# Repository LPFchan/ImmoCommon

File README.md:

# Immogen — Ninebot G30 BLE Immobilizer

**Immogen** is a three-part BLE immobilizer system for the Ninebot Max G30, consisting of **[Uguisu](https://github.com/LPFchan/Immogen/tree/main/Uguisu#readme)** (key fob), **[Guillemot](https://github.com/LPFchan/Immogen/tree/main/Guillemot#readme)** (deck receiver), and **[Whimbrel](https://github.com/LPFchan/Whimbrel)** (Web Serial provisioning app).

Guillemot sits inline between the battery and ESC via an XT60 splice. Without a valid BLE unlock from Uguisu, the scooter stays inoperable. Male/female pigtails keep the install reversible—no permanent modification required.

```
┌─────────────────┐       BLE advertisement        ┌──────────────────────┐
│  UGUISU (FOB)   │ ─────────────────────────────> │ GUILLEMOT (RECEIVER) │
│  XIAO nRF52840  │       (2.4 GHz, ~2 m)          │  XIAO nRF52840       │
└───────┬─────────┘                                └──────────┬───────────┘
        │                                                     │
        │                 ┌────────────────────┐              │
        └──────(USB-C)──> │ WHIMBREL (WEB APP) │ <──(USB-C)───┘
       (Provisioning)     │ Chrome / Edge      │    (Provisioning)
                          └────────────────────┘
```

## Repository Structure

| Path             | Description                                                                                                                                                                       |
| ---------------- | --------------------------------------------------------------------------------------------------------------------------------------------------------------------------------- |
| `Uguisu/`    | Key fob — firmware, KiCad, BOM. Button press → 2 s BLE broadcast → sleep. [README](https://github.com/LPFchan/Immogen/tree/main/Uguisu#readme)                                 |
| `Guillemot/` | Deck receiver — firmware, KiCad, BOM. Duty-cycled scan (5%), validates adverts → SR latch → power gate. [README](https://github.com/LPFchan/Immogen/tree/main/Guillemot#readme) |
| `lib/`       | Shared C++ library: AES-128-CCM MIC, provisioning loop, LittleFS counter storage                                                                                                  |
| `tools/`     | LED visualizer, BLE timing simulator, buzzer tuner (HTML); MIC test vectors (`gen_mic.py`)                                                                                        |
| `logs/`      | Technical writeups: architecture reviews, BLE power analysis, design decisions, migration guides, documentation reports                                                              |

## BLE Protocol

Advertisement-only; no persistent connection. Both devices share a company ID, a 2-byte magic prefix (`0x494D`), and a pre-shared key (PSK). Each advertisement carries a 13-byte payload after the manufacturer specific data header (company ID + magic):

| Offset | Size | Field   | Purpose                    |
| ------ | ---- | ------- | -------------------------- |
| 0      | 4    | counter | Anti-replay, monotonic (AAD)|
| 4      | 1    | command | 0x01 = Unlock, 0x02 = Lock (Encrypted) |
| 5      | 8    | mic     | AES-128-CCM auth tag       |

## Quick Start

Pre-built firmware is available on the [Releases](https://github.com/LPFchan/Immogen/releases) page. Use [Whimbrel](https://github.com/LPFchan/Whimbrel) to flash and provision keys via Web Serial.

**Build from source:**

```bash
# Deck receiver
cd Guillemot/firmware && pio run

# Key fob
cd Uguisu/firmware && pio run
```

## Roadmap

- Uguisu enclosure CAD (3D print).
- First-build validation: PPK2 power, BLE range through deck, pre-charge waveform.

## Safety & Legal

- Prototype security/power-interrupt device. Use at your own risk.
- Not affiliated with Segway-Ninebot.
- **Do not test lock behavior while riding.**

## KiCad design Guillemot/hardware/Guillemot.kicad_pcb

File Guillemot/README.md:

# Guillemot — Ninebot G30 BLE Immobilizer Receiver

Guillemot is the deck receiver in a three-part immobilizer system ([Uguisu](https://github.com/LPFchan/Immogen/tree/main/Uguisu) fob + [Whimbrel](https://github.com/LPFchan/Whimbrel) web app) for the Ninebot Max G30. It validates encrypted BLE advertisements from the fob and controls an SR latch that gates battery-to-ESC power via an inline XT60 splice. Male/female pigtails make it fully reversible—no permanent modification to the vehicle. Protocol and cryptography are handled by the shared [lib/](https://github.com/LPFchan/Immogen/tree/main/lib) in this monorepo ([Immogen](https://github.com/LPFchan/Immogen)).

---

## Hardware

### Placement

Mount Guillemot on the plastic underside of the deck for good 2.4 GHz RF.

### Components & BOM (~$20)

| Ref       | Part            | Notes                                                             | JLCPCB #         | Cost   |
| --------- | --------------- | ----------------------------------------------------------------- | ---------------- | ------ |
| U1        | XIAO nRF52840   | MCU: BLE scanning, latch control, buzzer PWM                      | Seeed            | $8.23  |
| U2        | SN74LVC2G02DCTR | SR latch: Q = unlock. 10 nF + 100 kΩ differentiator for POR pulse | C94600 (ext.)    | $0.53  |
| PS1       | TPSM365R6V3RDNR | Buck: 3–65 V in, 3.3 V/600 mA, 4 μA Iq. Feeds XIAO 3V3 directly.  | C18208843 (ext.) | $3.59  |
| Q1        | IPB042N10N3G    | Main MOSFET: 100 V/137 A, D2PAK, low-side GND return              | C69300 (ext.)    | $0.75  |
| Q2        | AO3422          | Pre-charge FET, inrush ~0.8 A. Driven by latch Q.                 | C37130 (ext.)    | $0.23  |
| Q3        | SI2309CDS       | Bleeder P-FET: disconnects 10 kΩ bleeder when locked (0 μA)       | C10493 (ext.)    | $0.23  |
| Q4        | 2N7002          | Gate drive                                                        | C8545            | $0.01  |
| Q5, Q6    | MMBT3904        | Buzzer driver                                                     | C20526           | $0.02  |
| BZ1       | FUET-1230       | Buzzer: 12×12×3 mm SMD, 4 kHz. Driven by MMBT3904                 | C391037 (ext.)   | $0.47  |
| D1        | BZT52C12-7-F    | 12 V Zener                                                        | C124196 (ext.)   | $0.11  |
| D2        | BZT52C10-7-F    | 10 V Zener                                                        | C155227 (ext.)   | $0.10  |
| D3, D4    | 1N4148W         | Gate isolation from buzzer rail sag                               | C81598           | $0.01  |
| D5        | SMBJ45A         | 45 V TVS diode for transient suppression                          | C114005 (ext.)   | $0.08  |
| C1        | 10 nF (0603)    | POR pulse differentiator                                          | C57112           | $0.003 |
| C2        | 100 µF (1210)   | Bulk decoupling. EMK325ABJ107MM-P 16V X5R ±20%                   | C90143 (ext.)    | $0.31  |
| C3, C4    | 1 µF (0603)     | RC delay bypass, gate isolation                                   | C15849           | $0.01  |
| R1–R3, R7 | 100 kΩ (0603)   | Gate drive, pull-ups, RC delay (τ = 100 ms)                       | C25803           | $0.006 |
| R4        | 1 MΩ (0603)     | P-FET gate pull-up                                                | C22935           | $0.001 |
| R5        | 10 kΩ (0603)    | Bleeder resistor                                                  | C25804           | $0.001 |
| R6        | 4.7 kΩ (0603)   | Piezo buzzer discharge resistor                                   | C23162           | $0.001 |
| R8        | 47 Ω 2 W (2512) | Pre-charge resistor, inrush ~0.77–0.89 A                         | C136992 (ext.)   | $0.10  |
| TP1–5     | XT60 + 12 AWG   | Pigtails and GND jumper                                           | Generic          | —      |
| —         | PCB             | 54×34 mm, 2 oz outer                                              | JLCPCB           | $1.60  |

JLCPCB P&P for SMT. Hand-solder XIAO edges, XT60 pigtails, and the GND jumper.

### PCB Layout

4-layer, 54×34 mm, 2 oz outer copper, designed for 30 A continuous.

- **12 AWG GND jumper (critical):** Main battery return bypasses inner layers. Run an external silicone wire from the `BAT-` XT60 pad to the MOSFET source pad.
- **Power traces:** `+BATT` and `ESC-` as top-layer pours. No high-current vias.
- **Clearance:** ≥ 0.6 mm between 42 V power and 3.3 V logic.
- **Pre-charge trace:** Q2 → R8 → `ESC-` routed at **1.0 mm** to survive initial ~40 W inrush surge.
- **RF keepout:** Strip copper on all layers under the XIAO's BLE antenna trace.
- **Assembly:** Single-sided (F.Cu) SMT for easy JLCPCB PCBA.

### Operation

- **Unlock flow:** Uguisu advert → MCU validates → SET latch → Q HIGH → pre-charge 100 ms → MOSFET ON → buzzer tone.
- **Lock flow:** Uguisu advert → MCU validates → buzzer tone → RESET latch → Q LOW → P-FET OFF, pre-charge OFF → MOSFET OFF.
- **Power (locked):** ~306 μA (buck Iq + 5% duty-cycled scan + latch). At 306 μA, a G30 (15.3 Ah) would theoretically take ~5.7 years to drain; battery self-discharge (~12 months) dominates in practice. See `logs/15-BLE_POWER_ANALYSIS_AND_DOCUMENTATION_DISCREPANCY.md` for derivation.
- **Buzzer timing:** Unlock tone ~34 ms after 10 V rail up; lock tone before RESET.

### Design Notes

- **EasyEDA → KiCad:** Schematics and PCBs are designed in KiCad. [easyeda2kicad](https://github.com/wokwi/easyeda2kicad) is used to import symbols and footprints from EasyEDA/LCSC. Example: `easyeda2kicad --full --lcsc_id=Cxxxx` (replace `Cxxxx` with the LCSC part number).
- **AO3422:** 55 V Vds provides margin over the 42 V bus when locked.
- **Gate drive R (100 kΩ):** Protects the 2N7002 and BZT Zeners.
- **POR circuit (10 nF + 100 kΩ):** 1 ms RC differentiator—brief pulse zeros the latch at power-on.
- **RC delay (100 kΩ + 1 μF):** 1N4148W bypass for fast turn-off.
- **Gate isolation (1N4148W + cap):** Buzzer draw exceeds bleeder supply; diode and 1 μF hold cap prevent gate sag during tones (Vgs ≈ 9.3 V).
- **Gate pull-down (MMBT3904):** Via Q̄/RC, discharges hold cap for instant OFF.
- **IPB042N10N3G:** Outperforms TO-220 standing upright in sealed deck enclosures when thermal pad is stitched to B.Cu. **IPB035N10NF2S (3.5 mΩ)** is the long-term successor depending on LCSC stock.

---

## Software

### Firmware

[PlatformIO](https://platformio.org/) project in `firmware/`

Scanning is duty-cycled (25 ms every 500 ms, 5% duty) for reliable detection. P(detect) = 100% per button press because `scanWindow (25 ms) ≥ advInterval (20 ms)` guarantees full phase coverage. The receiver rejects any payload with an invalid AES-CCM MIC or a counter less than or equal to the last seen value (anti-replay). The receiver is also protected against MCU hangs by an 8-second hardware Watchdog Timer (WDT) which triggers a clean reboot without disrupting the latch state.

### Protocol

Validation and crypto via shared [lib/](https://github.com/LPFchan/Immogen/tree/main/lib). See [Immogen README § BLE Protocol](https://github.com/LPFchan/Immogen#ble-protocol) for full specification.

### Onboarding

Use [Whimbrel](https://github.com/LPFchan/Whimbrel) for both tasks:

- **Firmware flashing:** Web-based flasher via Web Serial. Enter bootloader mode with a double-tap on reset.
- **Key provisioning:** Connect via USB; Whimbrel injects the shared AES-128 key. Physical presence is required. The firmware has no serial commands to read the key back.

---

## Safety & Notes

- Prototype security and power-interrupt device. Use at your own risk.
- Do not test lock behavior while riding.
- Not affiliated with Segway-Ninebot.
- Avoid committing KiCad per-user state (`*.kicad_prl`) or lock files.

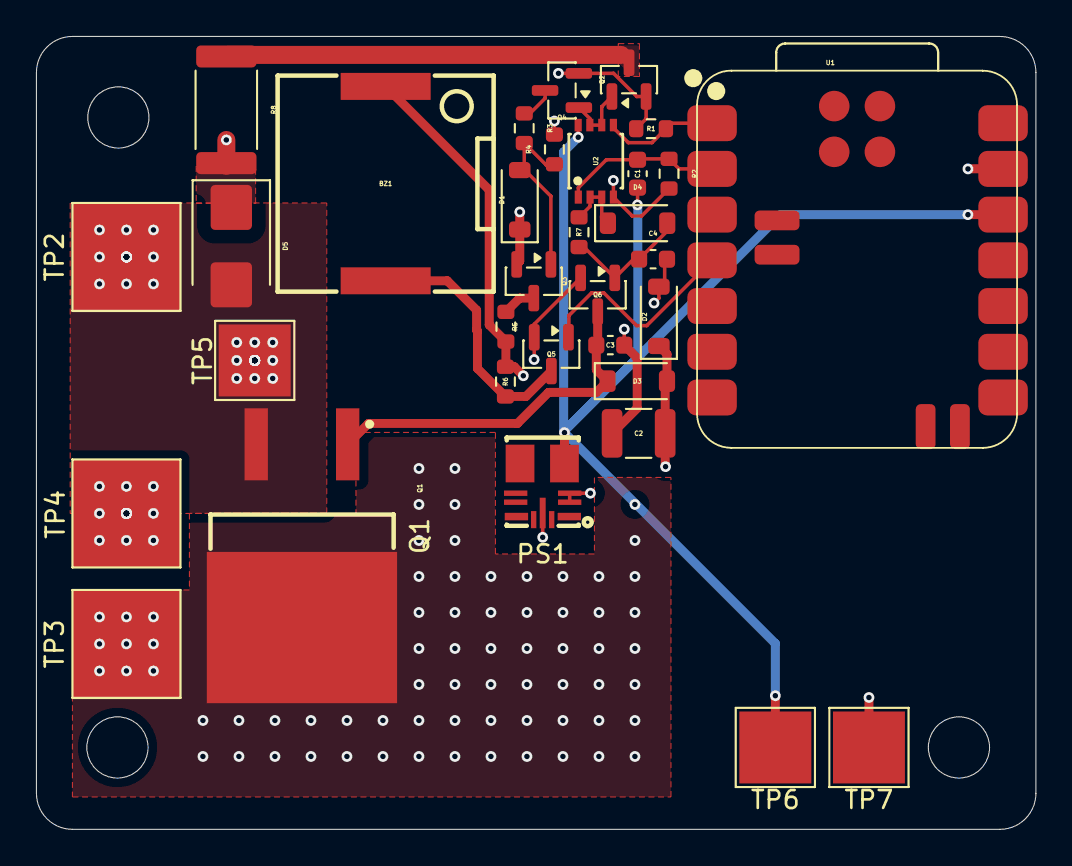
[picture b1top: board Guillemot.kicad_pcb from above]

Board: 4 copper layers, 55.5 x 44.0 mm, 33 parts (0 on the bottom side), 17 nets.

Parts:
BZ1: FUET-1230; BUZ-SMD_L12.0-W12.0_FUET-1230
C1: 10nF; C_0603_1608Metric
C2: 100µF; C_1210_3225Metric
C3, C4: 1uF; C_0603_1608Metric
D1: BZT52C12-7-F; D_SOD-123
D2: BZT52C10-7-F; D_SOD-123
D3, D4: 1N4148W; D_SOD-123
D5: SMBJ45A; D_SMB
PS1: TPSM365R6V3RDNR; QFN-11_L4.5-W3.5-P0.50-TL_TPSM365R6FRDNR
Q1: IPB042N10N3G; TO-263-2_L10.0-W9.1-P5.08-LS15.2-TL
Q2: AO3422; SOT-23
Q3: SI2309CDS; SOT-23
Q4: 2N7002; SOT-23
Q5, Q6: MMBT3904; SOT-23
R1, R2, R3, R7: 100k; R_0603_1608Metric
R4: 1M; R_0603_1608Metric
R5: 10k; R_0603_1608Metric
R6: 4.7k; R_0603_1608Metric
R8: 47 2W; R_2512_6332Metric
TP2: BAT-; TestPoint_Pad_6.0x6.0mm
TP3: ESC-; TestPoint_Pad_6.0x6.0mm
TP4: ESC+; TestPoint_Pad_6.0x6.0mm
TP5: WIRE; TestPoint_Pad_4.0x4.0mm
TP6: 3.3V; TestPoint_Pad_4.0x4.0mm
TP7: GND; TestPoint_Pad_4.0x4.0mm
U1: XIAO-nRF52840-SMD
U2: SN74LVC2G02DCTR; MSOP-8_L2.9-W2.8-P0.65-LS4.0-BR

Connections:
+BATT: D1.1 (K), PS1.2 (EN), PS1.3 (VIN), Q3.2 (S), R4.2, TP4.1
/3.3V: C1.2, PS1.4 (VOUT), TP6.1, U1.12 (3V3), U2.8 (VCC)
/10V_RAIL: BZ1.1 (+), C2.1, D2.1 (K), D3.2 (A), R5.2, R6.1
/10V_RAW: Q3.3 (D), R5.1
/BUZZER_SINK: BZ1.2, Q5.3 (C), R6.2
/ESC-: D5.1 (A1), Q1.4 (D), R8.2, TP3.1
/ISO_GATE: C3.1, D3.1 (K), Q1.1 (G), Q6.3 (C)
/MCU_D0: R1.1, U1.1 (P0.02_A0_D0), U2.5 (2A)
/MCU_D1: C1.1, R2.1, U1.2 (P0.03_A1_D1), U2.1 (1A)
/MCU_D3: Q5.1 (B), U1.4 (P0.29_A3_D3)
/NPN_BASE: C4.1, D4.2 (A), Q6.1 (B), R7.2
/PFET_CTRL: Q4.3 (D), R3.1
/PFET_GATE: D1.2 (A), Q3.1 (G), R3.2, R4.1
/PRECHARGE_OUT: Q2.3 (D), R8.1
/QBAR_LOCK: D4.1 (K), R7.1, U2.2 (1B), U2.3 (2Y)
/Q_UNLOCK: Q2.1 (G), Q4.1 (G), U2.6 (2B), U2.7 (1Y)
GND: C2.2, C3.2, C4.2, D2.2 (A), D5.2 (A2), PS1.10 (GND), Q1.3 (S), Q2.2 (S), Q4.2 (S), Q5.2 (E), Q6.2 (E), R1.2, R2.2, TP2.1, TP5.1, TP7.1, U1.13 (GND), U2.4 (GND)

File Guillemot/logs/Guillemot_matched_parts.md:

# Guillemot BOM - Matched Parts

## Matched Components


| Designator  | Comment         | Footprint                       | Part Name               | LCSC      | Description / Specs                                                                                                                | Qty | Type     | Total Cost |
| ----------- | --------------- | ------------------------------- | ----------------------- | --------- | ---------------------------------------------------------------------------------------------------------------------------------- | --- | -------- | ---------- |
| BZ1         | FUET-1230       | BUZ-SMD_L12.0-W12.0_FUET-1230   | FUET-1230               | C391037   | -20℃~~+70℃ 12mm 12mm 1V~~25V 3.3mm 3V 4kHz 5mA 75dB Passive (Externally Driven) Piezoelectric SMD,12x12mm Buzzers ROHS             | 5   | Extended | $2.3640    |
| C1          | 10nF            | 0603                            | 0603B103K500NT          | C57112    | 10nF 50V X7R ±10% 0603 Multilayer Ceramic Capacitors MLCC - SMD/SMT ROHS                                                           | 5   | Basic    | $0.0140    |
| C2          | 100µF           | 1210                            | EMK325ABJ107MM-P        | C90143    | 100uF 16V X5R ±20% 1210 Multilayer Ceramic Capacitors MLCC - SMD/SMT ROHS                                                          | 5   | Extended | $1.5285    |
| C3,C4       | 1uF             | 0603                            | CL10A105KB8NNNC         | C15849    | 1uF 50V X5R ±10% 0603 Multilayer Ceramic Capacitors MLCC - SMD/SMT ROHS                                                            | 5   | Basic    | $0.0720    |
| D1          | BZT52C12-7-F    | D_SOD-123                       | BZT52C12-7-F            | C124196   | -65℃~~+150℃ 100nA@1V 11.4V~~12.7V 12V 150Ω 25Ω 370mW Independent SOD-123 Zener Diodes ROHS                                         | 5   | Extended | $0.5538    |
| D2          | BZT52C10-7-F    | D_SOD-123                       | BZT52C10-7-F            | C155227   | -65℃~~+150℃ 10V 150Ω 200nA 20Ω 370mW 9.4V~~10.6V Independent SOD-123 Zener Diodes ROHS                                             | 5   | Extended | $0.5085    |
| D3,D4       | 1N4148W         | D_SOD-123                       | 1N4148W                 | C81598    | 1.25V@150mA 100V 150mA 1uA@75V 2A 4ns 500mW Independent SOD-123 Switching Diodes ROHS                                              | 10  | Basic    | $0.1100    |
| D5          | SMBJ45A         | D_SMB                           | SMBJ45A                 | C114005   | -65℃~+150℃ 1uA 45V 55.3V 600W@10/1000us 72.7V 8.3A@10/1000us TVS Unidirectional DO-214AA(SMB) ESD and Surge Protection             | 5   | Extended | $0.4221    |
| PS1         | TPSM365R6V3RDNR | CONV_TPSM365R6V3RDNR            | TPSM365R6V3RDNR         | C18208843 | -40℃~~+125℃ 1MHz 2mm 3.3V 3.5mm 3.6V~~65V 4.5mm 4uA 600mA 80.2% Buck Overheat protection、Over Current Protection ±1.5%             | 5   | Extended | $17.9375   |
| Q1          | IPB042N10N3G    | TO-263-2                        | IPB042N10N3G            | C69300    | -55℃~+175℃ 1 N-channel 100V 117nC 137A 214W 3.5V 4.2mΩ@10V 41pF 8.41nF TO-263-3 MOSFETs ROHS                                       | 5   | Extended | $3.7630    |
| Q2          | AO3422          | SOT-23                          | AO3422                  | C37130    | 1 N-channel 10A 12.6pF 160mΩ@4.5V 2V [3.3nC@4.5V](mailto:3.3nC@4.5V) 300pF 55V N-Channel SOT-23 MOSFETs ROHS                       | 5   | Extended | $1.1376    |
| Q3          | SI2309CDS       | SOT-23                          | SI2309CDS-T1-GE3        | C10493    | -55℃~+150℃ 1 P-Channel 1.6A 1.7W 20pF 210pF 28pF 3V [4.1nC@4.5V](mailto:4.1nC@4.5V) 450mΩ@4.5V 60V P-Channel SOT-23-3 MOSFETs ROHS | 5   | Extended | $1.1333    |
| Q4          | 2N7002          | SOT-23                          | 2N7002                  | C8545     | 1 N-channel 115mA 2.5V 225mW 50pF 5pF 5Ω@10V 60V SOT-23 MOSFETs ROHS                                                               | 5   | Basic    | $0.0660    |
| Q5,Q6       | MMBT3904        | SOT-23                          | MMBT3904(RANGE:100-300) | C20526    | -55℃~+150℃ 1 NPN 100 100nA 200mA 200mW 300MHz 300mV 40V 6V NPN SOT-23 Bipolar (BJT) ROHS                                           | 5   | Basic    | $0.0950    |
| R1,R2,R3,R7 | 100k            | 0603                            | 0603WAF1003T5E          | C25803    | -55℃~+155℃ 100kΩ 100mW 75V Thick Film Resistor ±1% ±100ppm/℃ 0603 Chip Resistor - Surface Mount ROHS                               | 5   | Basic    | $0.0280    |
| R4          | 1M              | 0603                            | 0603WAF1004T5E          | C22935    | -55℃~+155℃ 100mW 1MΩ 75V Thick Film Resistor ±1% ±100ppm/℃ 0603 Chip Resistor - Surface Mount ROHS                                 | 5   | Basic    | $0.0065    |
| R5          | 10k             | 0603                            | 0603WAF1002T5E          | C25804    | -55℃~+155℃ 100mW 10kΩ 75V Thick Film Resistor ±1% ±100ppm/℃ 0603 Chip Resistor - Surface Mount ROHS                                | 5   | Basic    | $0.0065    |
| R6          | 4.7k            | 0603                            | 0603WAF4701T5E          | C23162    | -55℃~+155℃ 100mW 4.7kΩ 75V Thick Film Resistor ±1% ±100ppm/℃ 0603 Chip Resistor - Surface Mount ROHS                               | 5   | Basic    | $0.0065    |
| R8          | 472W            | 2512                            | RC2512JK-7W47RL         | C136992   | -55℃~+155℃ 200V 2W 47Ω Thick Film Resistor ±200ppm/℃ ±5% 2512 Chip Resistor - Surface Mount ROHS                                   | 5   | Extended | $0.5184    |
| U2          | SN74LVC2G02DCTR | MSOP-8_L2.9-W2.8-P0.65-LS4.0-BR | SN74LVC2G02DCTR         | C94600    | -40℃~~+125℃ 1.2V、1.9V、2.3V、2.4V、3.8V 1.65V~~5.5V 1.7V~2V 10uA 2 2 300mV、400mV、450mV、550mV 32mA 32mA 4.4ns@5V,50pF 74LVC            | 5   | Extended | $2.6565    |


## Unmatched Components


| Designator | Comment           |
| ---------- | ----------------- |
| U1         | XIAO-nRF52840-SMD |

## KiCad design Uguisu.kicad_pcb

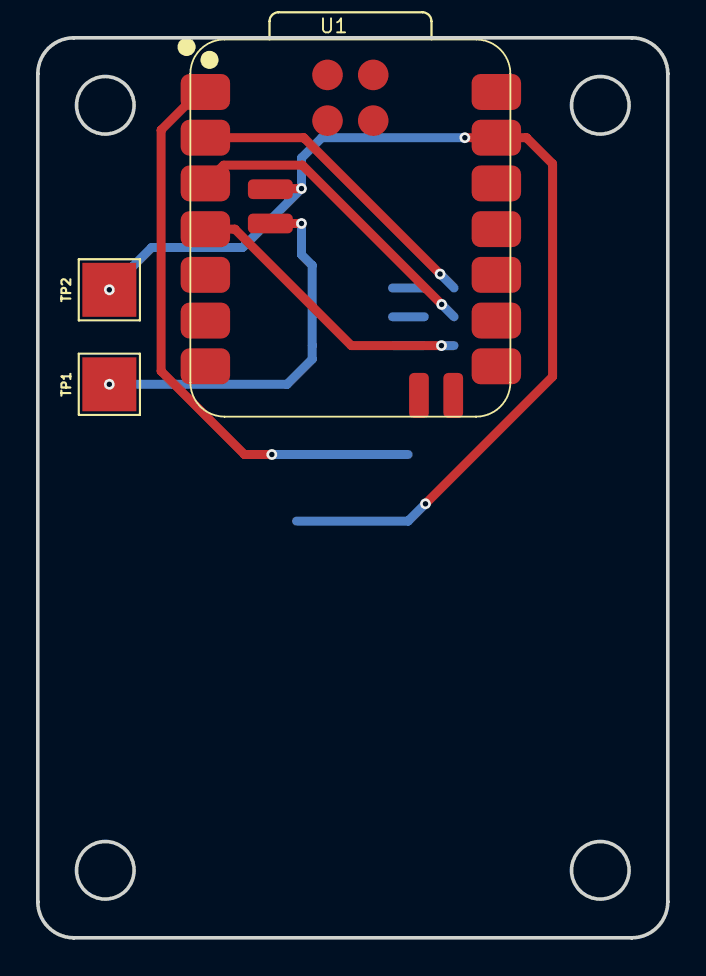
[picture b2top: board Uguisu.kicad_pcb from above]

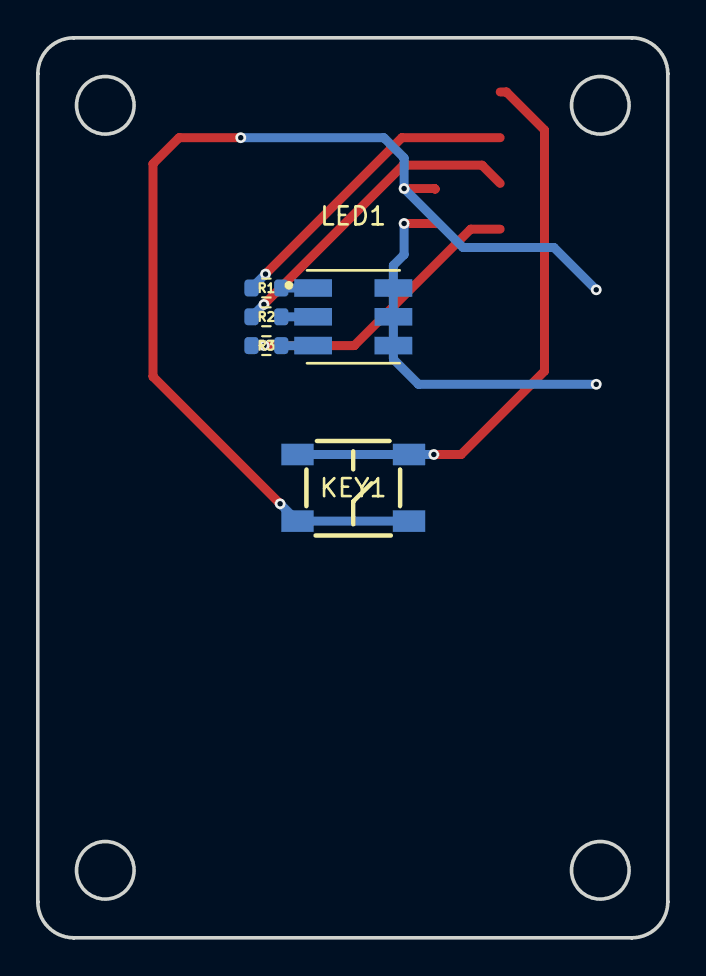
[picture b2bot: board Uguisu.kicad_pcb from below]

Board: 2 copper layers, 35.0 x 50.0 mm, 8 parts (5 on the bottom side), 9 nets.

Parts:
KEY1: SKQGABE010; KEY-SMD_4P-L5.2-W5.2-P3.70-LS6.4
LED1: XL-5050RGBC; LED-ARRAY-SMD_6P-L5.0-W5.0-TL-RD_3
R1, R3: 120; R_0603_1608Metric
R2: 330; R_0603_1608Metric
TP1: +BATT; TestPoint_Pad_3.0x3.0mm
TP2: GND; TestPoint_Pad_3.0x3.0mm
U1: XIAO-nRF52840-SMD

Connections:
+BATT: LED1.4 (G+), LED1.5 (R+), LED1.6 (B+), TP1.1, U1.32 (BAT)
/MCU_D0: KEY1.1, KEY1.2, U1.1 (P0.02_A0_D0)
/MCU_D1: R1.2, U1.2 (P0.03_A1_D1)
/MCU_D2: R2.2, U1.3 (P0.28_A2_D2)
/MCU_D3: R3.1, U1.4 (P0.29_A3_D3)
GND: KEY1.3, KEY1.4, TP2.1, U1.13 (GND), U1.33 (GND)
unnamed: LED1.1 (B-), R1.1
unnamed: LED1.3 (G-), R3.2
unnamed: LED1.2 (R-), R2.1

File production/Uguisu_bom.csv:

Designator,Footprint,Quantity,Value,LCSC Part #
KEY1,KEY-SMD_4P-L5.2-W5.2-P3.70-LS6.4,1,SKQGABE010,C115351
LED1,LED-ARRAY-SMD_6P-L5.0-W5.0-TL-RD_3,1,XL-5050RGBC,C2843868
"R1, R3",0603,2,120,
R2,0603,1,330,
TP1,TestPoint_Pad_3.0x3.0mm,1,+BATT,
TP2,TestPoint_Pad_3.0x3.0mm,1,GND,
U1,XIAO-nRF52840-SMD,1,XIAO-nRF52840-SMD,

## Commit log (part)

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2026-03-06 Initial Uguisu KiCad project
    Add KiCad project sources with a minimal README and ignore rules for per-user KiCad artifacts.
2026-03-06 Add PROTOCOL.md, Whimbrel provisioning, build fix (TinyUSB/SPI/bonding), config placeholders
    Made-with: Cursor
2026-03-06 Provisioning: Whimbrel-only init, drop secrets headers, zero-key auto prov, verify+BOOTED, CRC-16 checksum
    Made-with: Cursor
2026-03-06 Add release workflow: build firmware and publish on v* tags
    Made-with: Cursor
2026-03-06 Fix release: disable generate_release_notes (GITHUB_TOKEN 403)
    Made-with: Cursor
2026-03-06 Release workflow: grant contents: write so GITHUB_TOKEN can create releases
    Made-with: Cursor
2026-03-06 Release: use RELEASE_TOKEN secret (PAT); add RELEASE-SETUP.md
    Made-with: Cursor
2026-03-06 refactor: extract common modules and update documentation
    - Extracted duplicated crypto, provisioning, and storage logic into a shared `lib/ImmoCommon` module
    - Refactored `main.cpp` to use the new shared modules
    - Updated `README.md` to use the unified structure and tone
    - Added explanatory comments to `platformio.ini` regarding `extra_scripts.py`
    Made-with: Cursor
2026-03-06 ci: fetch submodules on release
    Made-with: Cursor
2026-03-06 Refactor: Extract USB provisioning loop to reusable function
    Made-with: Cursor
2026-03-06 Refactor: Use ensure_provisioned() helper from ImmoCommon
    Made-with: Cursor
2026-03-06 Docs: Cross-link related repositories
    Made-with: Cursor
2026-03-06 Docs: Standardize format and remove bloat
    Made-with: Cursor
2026-03-06 Docs: Enrich README with hardware/power details
    Made-with: Cursor
2026-03-06 CI: Fix GitHub Actions permissions to allow creating releases
    Made-with: Cursor
2026-03-06 Drop device_id across protocol, crypto, storage, provisioning
    - Crypto: MSG_LEN 7→5, PAYLOAD_LEN 11→9, nonce/msg without device_id
    - Storage: CounterRecord(counter,crc32) only; lastCounter(), update(counter), seed(counter)
    - Provisioning: PROV:key:counter:checksum (no device_id)
    - gen_mic.py: remove --device-id, payload 9 bytes
    Breaking: re-provision required for existing devices
    Made-with: Cursor
2026-03-06 docs: update README BLE payload (9 bytes, no device ID)
    Made-with: Cursor
2026-03-06 Add ERR:STORAGE on provisioning failure; document append behavior in CounterStore
    Made-with: Cursor
2026-03-06 Update ImmoCommon submodule; remove dead PAYLOAD_LEN/MIC_LEN
    Made-with: Cursor
2026-03-07 Only print ERR:STORAGE when on_success is non-null
    Made-with: Cursor
2026-03-07 Minor fixes: remove g_has_provisioning, add button timeout const, LED error loop on InternalFS fail, update ImmoCommon
    Made-with: Cursor
2026-03-07 Add default-case comment; update ImmoCommon submodule
    Made-with: Cursor
2026-03-07 Replace README with combined design doc content
    Made-with: Cursor
2026-03-07 Remove PROTOCOL.md (moved to ImmoCommon), update protocol spec link
    Made-with: Cursor
2026-03-07 Update KiCad PCB
    Made-with: Cursor
2026-03-07 Improve BLE protocol section readability, drop fob/receiver parentheticals
    Made-with: Cursor
2026-03-07 Update ImmoCommon submodule
    Made-with: Cursor
2026-03-07 Button D0, RGB LED (LED1), config and README BOM updates
    Made-with: Cursor
2026-03-07 Restore KiCad schematic and PCB
    Made-with: Cursor
2026-03-07 docs: update BOM pricing with per-board breakdown and resistor notes
    Made-with: Cursor
2026-03-07 LED pin order and docs: D1=Blue, D2=Red, D3=Green; R1=Blue, R2=Red, R3=Green; LED1 pins 1/2/3
    Made-with: Cursor
2026-03-07 Update README BOM costs to unit price
    Made-with: Cursor
2026-03-07 Sync README BOM with JLCPCB review and add fabrication docs
    Made-with: Cursor
2026-03-08 Update KiCad project, README, production outputs; add fix_readme_cost.py
    Made-with: Cursor
2026-03-08 docs: add architecture critique, update readme and pcb files
    Made-with: Cursor
2026-03-08 build: replace extra_script hack with TinyUSB config flags
    Made-with: Cursor
2026-03-08 Fix `File` class naming collision natively
    - Removes fragile Python script (`extra_script.py`) used to intercept framework compilation
    - Updates Uguisu to use shared configuration macro from `ImmoCommon`
    - Disables Mass Storage Class (MSC) via TinyUSB built-in config macro `immo_tusb_config.h`
    - Adds `SPI` dependency to PlatformIO and sets LDF to `deep+`
    Made-with: Cursor
2026-03-08 fix: strict checksum length in provisioning parser (Fix 4)
    Change strlen(checksum_hex) < 4 to != 4 to reject trailing garbage.
    Accepts exactly 4 hex chars for CRC-16 checksum field.
    Made-with: Cursor
2026-03-08 fix: persist counter before advertising (Fix 2)
    - Move g_store.update(counter) before start_advertising_once to avoid
    counter reuse on power loss during advertise delay
    - Update ImmoCommon submodule for strict checksum length (Fix 4)
    Made-with: Cursor
2026-03-09 refactor: use ImmoCommon prov/util helpers, normalize PSK storage path
    - on_provision_success: delegate to immo::prov_write_and_verify()
    - load_provisioning: delegate to immo::prov_load_key()
    - PSK storage path changed from /ug_prov.bin to /prov.bin (re-provisioning required)
    - Remove local PROV_MAGIC (now immo::PROV_MAGIC in ImmoCommon)
    - key_is_all_zeros: thin wrapper over immo::is_key_blank()
    - led_error_loop: replaced with immo::led_error_loop(PIN_ERROR_LED)
2026-03-09 refactor: add shared defaults and prov_load_key_or_zero helper
    - Add DEFAULT_PROV_PATH, DEFAULT_PROV_TIMEOUT_MS to immo_provisioning.h
    - Add DEFAULT_COUNTER_LOG_MAX_BYTES to immo_storage.h
    - Add prov_load_key_or_zero() to eliminate duplicated load-or-zero pattern
    in Uguisu and Guillemot main.cpp
2026-03-09 refactor: use ImmoCommon shared defaults and prov_load_key_or_zero
    Bump ImmoCommon submodule to b52ef26. Replace local PROV_STORAGE_PATH,
    COUNTER_LOG_MAX_BYTES, PROV_TIMEOUT_MS, and k_default_psk with their
    immo:: counterparts. Simplify load_provisioning() via prov_load_key_or_zero.
2026-03-09 refactor: use ImmoCommon shared defaults and prov_load_key_or_zero
    Bump ImmoCommon submodule to b52ef26. Replace local PROV_STORAGE_PATH,
    COUNTER_LOG_MAX_BYTES, PROV_TIMEOUT_MS, and k_default_psk with their
    immo:: counterparts. Simplify load_psk_from_storage() via prov_load_key_or_zero.
2026-03-09 Remove unused UGUISU_BUILD_PIO build flag from platformio.ini
2026-03-09 feat: add RGB LED effects with interactive visualizer
    - Add led_effects.h: active-low PWM fade/pulse helpers for all boot states
    (unlock green, lock red, provisioning blue, low-battery pulse, error blink)
    - Add tools/led_visualizer.html: browser-based timing tuner with live preview,
    sync rise/fall toggle, and generated C++ define output
    - Wire led::init(), led::error_loop(), and led_effects.h include into main.cpp
    - Update README with LED behaviour table and complete annotated boot flow
2026-03-09 refactor: rename config header to uguisu_nrf52840.h, fix readVbat_mv, move system_off
    - Rename uguisu_config.example.h → uguisu_nrf52840.h to clearly identify it
    as the nRF52840 board-specific defaults
    - Fix readVbat_mv(): toggle VBAT_ENABLE (P0.14) around the ADC read to
    enable the PMOS-gated 1MΩ/1MΩ divider on XIAO nRF52840; add 1 ms settle
    delay; guard with #ifdef for portability
    - Move system_off() from main.cpp into uguisu_nrf52840.h alongside the
2026-03-09 tune: set BLE scan timing to 500 ms interval / 20 ms window
    Reduces scan interval from 2000→500 ms and window from 20→20 ms
    (window unchanged) to improve detection latency. Duty cycle rises
    from 1% to 4%, still well within scooter battery budget.
2026-03-09 Increase BLE scan window from 20ms to 25ms
    Made-with: Cursor
2026-03-09 Rename project to Immogen, update README and docs
    Made-with: Cursor
2026-03-09 Combine lib/tools into tools/ at repo root
    Made-with: Cursor
2026-03-09 Add monorepo migration report (13-MONOREPO_MIGRATION_REPORT.md)
    Made-with: Cursor
2026-03-09 docs: overhaul monorepo README as project entry point
    - Add project overview, architecture diagram, repository structure
    - Link to Guillemot and Uguisu READMEs for component details
    - Move releases info to Quick Start, pre-built firmware first
    - Remove duplicate content; point readers to component docs
    Made-with: Cursor
2026-03-09 docs: migration extract + Guillemot/monorepo updates
    - Add logs/14-DETAILED_DOC_EXCLUSIVE_CONTENT.md (EasyEDA→KiCad remains)
    - Guillemot README: PCB layout (pre-charge trace 1.0mm, single-sided SMT),
    design notes (inrush, RC bypass, gate isolation Vgs, gate pull-down,
    MOSFET successor IPB035N10NF2S)
    - Monorepo README: TBD section
    Made-with: Cursor
2026-03-09 docs: add master doc consolidation verification report
    Verify that all content from standalone BLE_Immobilizer_G30_Detailed(10).md
    is present in the monorepo documentation. Document the audit scope,
    section-by-section coverage mapping, corrected values (based on real
    measurement via logs/15), and minor discarded items (conformal coat,
    QSPI details, ephemeral key storage—already in Whimbrel README).
    Master document deleted after audit completion.
2026-03-09 docs: add Whimbrel demo branch sync guide
    Documents the process for merging main into the demo branch and
    re-enabling DEMO_MODE across all affected files. Includes the CSS
    corruption gotcha discovered during the March 2026 sync where
    -X theirs silently dropped .release-item and .progress-container
    rules from style.css.
2026-03-09 docs: streamline root README for clarity and concision
    Merged the redundant Components table into Repository Structure, removed
    the duplicate Further Reading section, dropped excessive horizontal rules,
    and renamed TBD to Roadmap.
2026-03-09 docs: remove test vectors section from root README
2026-03-09 Update README
    Made-with: Cursor
2026-03-09 docs: remove bold formatting from repository paths in README table
2026-03-09 docs: remove cross-reference to sub-READMEs for protocol spec
    The Immogen README is the source of truth for the BLE protocol.
    Guillemot and Uguisu READMEs already correctly reference back to
    the main Immogen README for protocol details—no need for bidirectional
    references.
2026-03-09 docs: improve logs/ folder description in README
    Better reflects actual content: technical writeups, architecture reviews,
    power analysis, design decisions, migration guides, and documentation
    reports—not just migration reports.
2026-03-09 Add last modified date/time to logs, move below heading
    Made-with: Cursor
2026-03-09 Update C2 to EMK325ABJ107MM-P, add no-hardware-edits rule, add codebase docs
    - C2: EMK325ABJ107MM-P 100µF 16V X5R (was CL32A107MPVNNNE 10V)
    - Cursor rule: do not modify files under hardware/
    - Guillemot: KiCad schematic/PCB LCSC C90143, README, matched parts
    - logs/18-CODEBASE_TECHNICAL_DOCUMENTATION.md
    Made-with: Cursor
2026-03-10 fix(arch): implement approved architecture and UX fixes
    - Added Watchdog Timer (WDT) to Guillemot to recover from firmware hangs
    - Updated button timing thresholds (700ms long press, 2000ms timeout)
    - Improved button UX with early exit on long press and <200ms press handling
    - Fixed LittleFS counter log rotation power-failure vulnerability
    - Added IMMOGEN_MAGIC prefix to MSD payload for better filtering
    - Upgraded payload security from CBC-MAC to AES-CCM CTR-mode encryption
2026-03-10 docs: update readmes with architecture and UX fixes
    - Documented new 700ms long press and 2s timeout behavior
    - Updated payload structure documentation to mention CTR encryption and AAD
    - Updated protocol section to mention the 2-byte magic prefix (0x494D)
    - Documented the WDT behavior in Guillemot's receiver logic
    Made-with: Cursor
2026-03-10 docs: finalize architecture assessments and technical fixes
